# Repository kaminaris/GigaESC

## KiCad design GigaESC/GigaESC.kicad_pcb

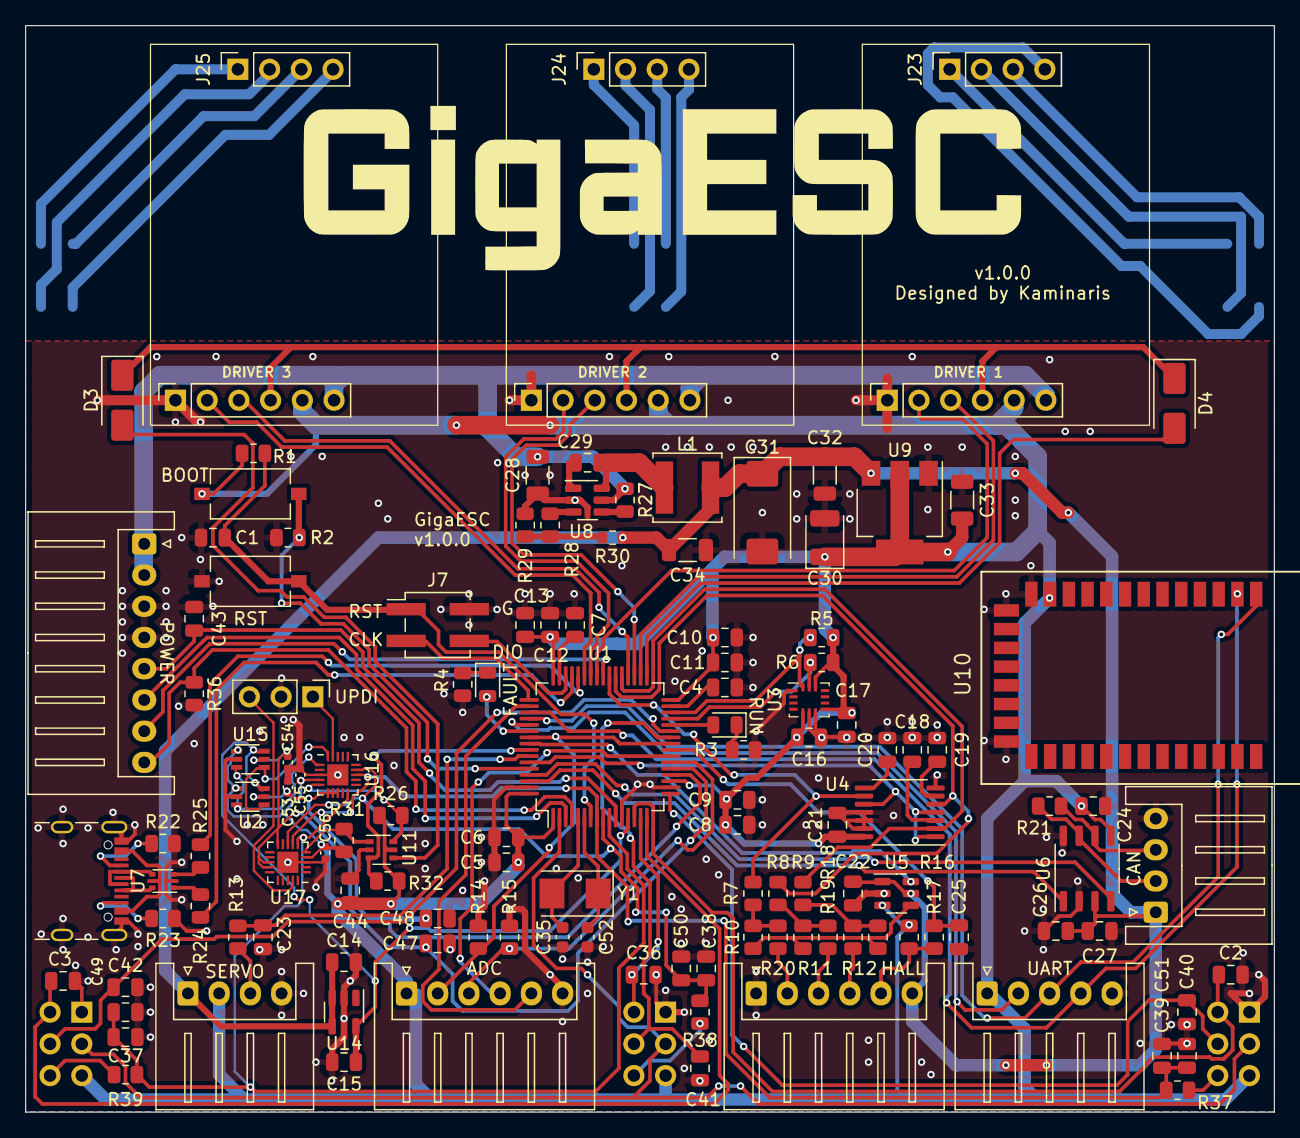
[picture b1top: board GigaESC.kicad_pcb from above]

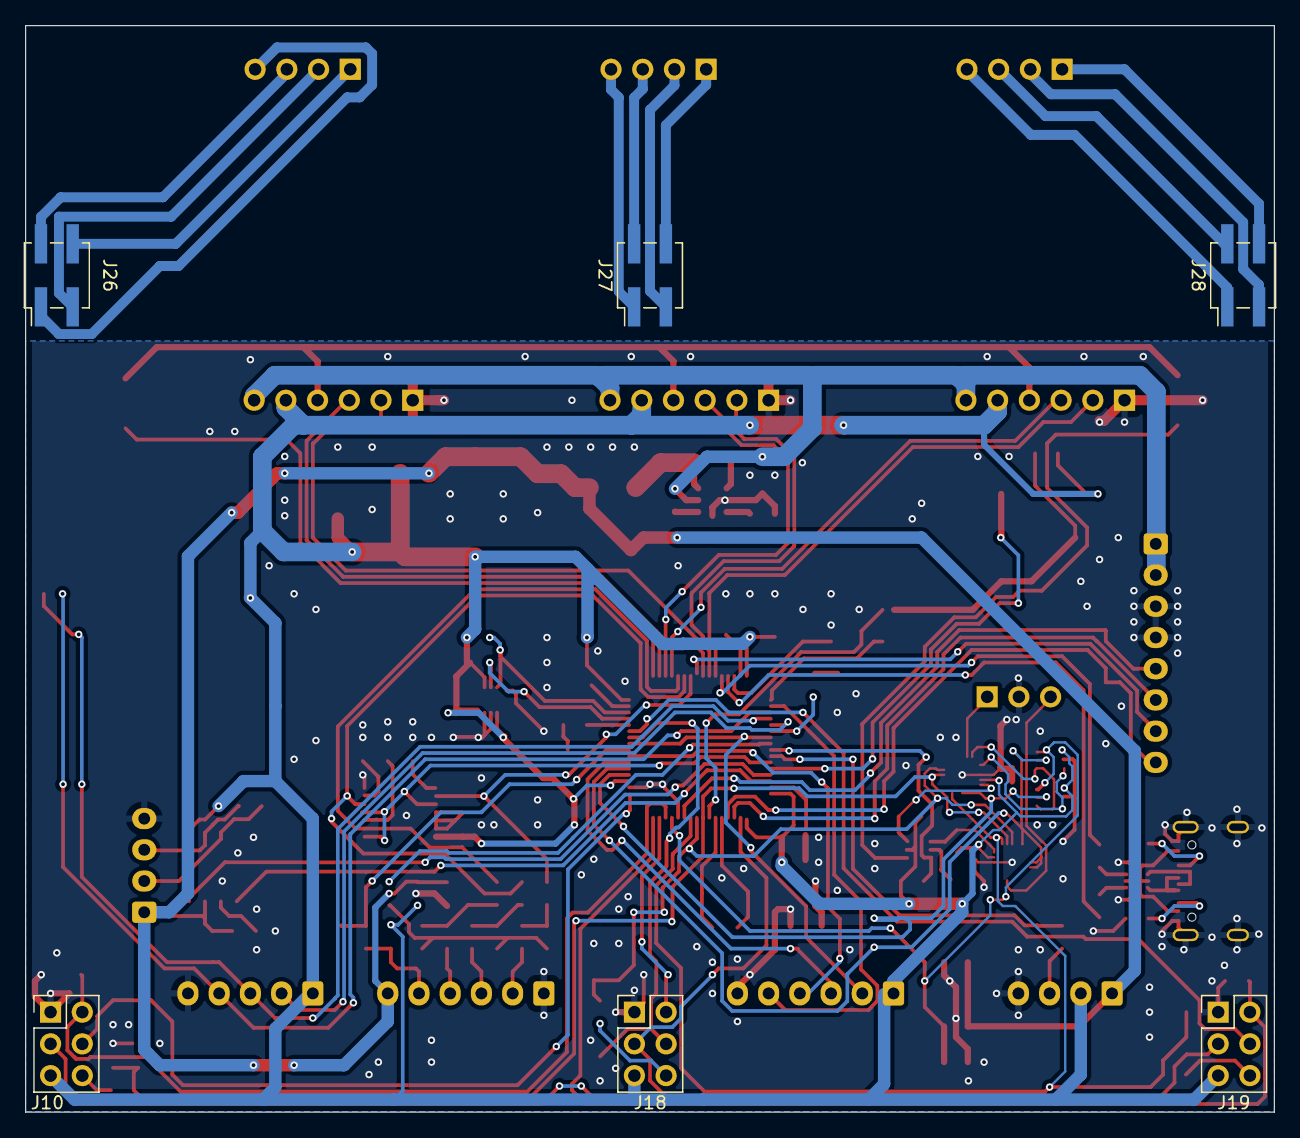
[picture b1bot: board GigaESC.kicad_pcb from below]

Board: 2 copper layers, 100.0 x 87.0 mm, 134 parts (6 on the bottom side), 110 nets.

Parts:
C1, C6, C9, C11, C13, C16, C17, C21, C22, C23, C24, C26, C44: 100n; C_0805_2012Metric
C2, C3, C36, C37, C38, C39, C40, C41, C42, C43: 1n; C_0805_2012Metric
C4, C7, C14, C15, C25, C47, C48: 1u; C_0805_2012Metric
C5, C8, C10, C12: 10n; C_0805_2012Metric
C18, C19, C20: 5n6; C_0805_2012Metric
C27: 2.2u; C_0805_2012Metric
C28: 47u 25V; C_1206_3216Metric
C29: 100n 100V; C_0805_2012Metric
C30: 100uF 6.3V Tant; CP_EIA-3528-15_AVX-H
C31: 100uF 25V Tant; CP_EIA-7343-31_Kemet-D
C32, C33, C34: 22u 25V; C_1206_3216Metric
C35, C52: 20p; C_0603_1608Metric
C49, C50, C51: 220p 50v; C_0805_2012Metric
C53, C54, C55, C56: 1u; C_0402_1005Metric
D1: L_RUN; LED_0805_2012Metric
D2: L_FAULT; LED_0805_2012Metric
D3, D4: SS14; D_SMA
J1: ServoConn; JST_XH_S4B-XH-A_1x04_P2.50mm_Horizontal
J2: AuxConn; JST_XH_S8B-XH-A_1x08_P2.50mm_Horizontal
J3, J14, J16: Input; PinSocket_1x06_P2.54mm_Vertical
J4: ADCConn; JST_XH_S6B-XH-A_1x06_P2.50mm_Horizontal
J5: HallConn; JST_XH_S6B-XH-A_1x06_P2.50mm_Horizontal
J6: UartSpi; JST_XH_S5B-XH-A_1x05_P2.50mm_Horizontal
J7: JTAG; PinHeader_2x02_P2.54mm_Vertical_SMD
J8: CANConn; JST_XH_S4B-XH-A_1x04_P2.50mm_Horizontal
J9: USBC Socket; USB_C_Receptacle_GCT_USB4105-xx-A_16P_TopMnt_Horizontal
J10, J18, J19: PhaseConn1; PinHeader_2x03_P2.54mm_Vertical
J12: UpdiConn; PinHeader_1x03_P2.54mm_Vertical
J23, J24, J25: Output; PinSocket_1x04_P2.54mm_Vertical
J26, J27, J28: OutputDown; PinHeader_2x02_P2.54mm_Vertical_SMD
L1: 5.6uH; L_Sunlord_SWPA5040S
R1, R3, R4, R14, R15, R16, R26, R31, R32, R36: 10k; R_0805_2012Metric
R2: 3.3k; R_0805_2012Metric
R5, R6: 4.7k; R_0805_2012Metric
R7, R8, R9, R10, R11, R12, R17, R37, R38, R39: 2.2k; R_0805_2012Metric
R13: 220; R_0805_2012Metric
R18, R19, R20: 100; R_0805_2012Metric
R21: 120; R_0805_2012Metric
R22, R23: 5.1k; R_0805_2012Metric
R24, R25: 22; R_0805_2012Metric
R27: 100k; R_0805_2012Metric
R28: 33k; R_0805_2012Metric
R29: 7.68k; R_0805_2012Metric
R30: 40.2k; R_0603_1608Metric
SW1: BOOT; SW_Tactile_SPST_NO_Straight_CK_PTS636Sx25SMTRLFS
SW3: RST; SW_Tactile_SPST_NO_Straight_CK_PTS636Sx25SMTRLFS
U1: STM32F405RGT6; LQFP-64_10x10mm_P0.5mm
U2: TPL0401A-10DCKR; Texas_R-PDSO-G6
U3: LSM6DS3TR-C; Bosch_LGA-14_3x2.5mm_P0.5mm
U4: SN74CBT3126PWR; TSSOP-14_4.4x5mm_P0.65mm
U5: RS2057XH; SOT-23-6
U6: TJA1051T-3; SOP-8_3.9x4.9mm_P1.27mm
U7: USBLC6-2P6; SOT-666
U8: ZTP7193Y; TSOT-23-6
U9: AMS1117-3.3; SOT-223-3_TabPin2
U10: HM-10; HM10
U11: SN74LVC1G332DCKR; SOT-363_SC-70-6
U14: LM4128AMF-3.3; SOT-23-5
U15: TPL0401B-10DCKR; Texas_R-PDSO-G6
U16, U17: ATTINY1616-MNR; VQFN-20-1EP_3x3mm_P0.4mm_EP1.7x1.7mm
Y1: X50328MSB2GI; Crystal_SMD_5032-2Pin_5.0x3.2mm

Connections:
+3.3V: C5.2, C6.2, C8.2, C9.2, C10.2, C11.2, C12.2, C13.2, C16.1, C17.1, C21.1, C24.1, C30.1, C33.1, C44.1, C55.1, C56.1, J1.2, J3.5, J4.1, J6.1, J10.5, J14.5, J16.5, J18.5, J19.5, R1.1, R5.1, R6.1, R16.1, R26.1, R31.1, R32.1, SW1.1, U1.1 (VBAT), U1.19 (VDD), U1.32 (VDD), U1.48 (VDD), U1.64 (VDD), U2.1 (VDD), U3.5 (VDDIO), U3.8 (VDD), U3.12 (CSB), U4.14 (VCC), U5.3 (NC), U6.5 (VIO), U9.2 (VO), U10.12 (VCC), U11.5 (VCC), U15.1 (VDD), U16.4 (VCC), U17.4 (VCC)
+3.3VADC: C15.1, U1.13 (VDDA), U2.6 (H), U14.5 (VREF), U15.6 (H)
+5V: C14.1, C22.1, C26.1, C27.1, C31.1, C32.1, C34.1, J1.1, J5.6, J8.1, L1.2, R30.2, U5.1 (NO), U5.5 (V+), U6.3 (VCC), U9.3 (VI), U14.3 (EN), U14.4 (VIN)
+15V: C28.1, J2.1, J2.2, J3.6, J14.6, J16.6, R27.1, U8.5 (IN)
/HardwareProtection/UPDI: J12.1, U16.19 (~RESET/PA0)
/HardwareProtection/UPDI2: J12.3, U17.19 (~RESET/PA0)
AUX_ENABLE: J2.6, U1.3 (PC14)
AUX_FAULT: J2.7, U1.40 (PC9)
BOOT: R2.1, SW1.2, U1.60 (BOOT0)
CANRx: U1.61 (PB8), U6.4 (RXD)
CANTx: U1.62 (PB9), U6.1 (TXD)
CLEAR_HW_FAULT: J2.8, R36.1, U1.4 (PC15)
CURR1: J10.6, R37.1
CURR1_FILTERED: C39.1, C51.1, R37.2, U1.8 (PC0), U16.13 (PB1), U17.7 (PA6)
CURR2: J18.6, R38.1
CURR2_FILTERED: C38.1, C50.1, R38.2, U1.9 (PC1), U16.14 (PB0), U17.8 (PA7)
CURR3: J19.6, R39.1
CURR3_FILTERED: C37.1, C49.1, R39.2, U1.10 (PC2), U16.10 (PB4), U17.6 (PA5)
CURR_TRIP_HIGH: C48.1, C53.1, U1.20 (PA4), U2.5 (W), U16.6 (PA5), U16.7 (PA6), U16.8 (PA7)
CURR_TRIP_LOW: C47.1, C54.1, U1.21 (PA5), U15.5 (W), U17.10 (PB4), U17.13 (PB1), U17.14 (PB0)
EXT2_MOSI: J6.2, U1.53 (PC12)
EXT2_RX_MISO: J6.3, U1.52 (PC11), U10.1 (UART_TX)
EXT2_TX_SCK: J6.4, U1.51 (PC10), U10.2 (UART_RX)
GND: C1.2, C2.2, C3.2, C4.2, C5.1, C6.1, C7.2, C8.1, C9.1, C10.1, C11.1, C12.1, C13.1, C14.2, C15.2, C16.2, C17.2, C18.2, C19.2, C20.2, C21.2, C22.2, C23.2, C24.2, C25.2, C26.2, C27.2, C28.2, C30.2, C31.2, C32.2, C33.2, C34.2, C35.1, C36.2, C37.2, C38.2, C39.2, C40.2, C41.2, C42.2, C43.2, C44.2, C47.2, C48.2, C49.2, C50.2, C51.2, C52.2, C53.2, C54.2, C55.2, C56.2, J1.4, J2.3, J2.4, J3.1, J4.6, J5.1, J6.5, J7.2, J8.4, J9.A1 (GND), J9.A12 (GND), J9.B1 (GND), J9.B12 (GND), J9.S1 (SHIELD), J10.1, J12.2, J14.1, J16.1, J18.1, J19.1, R2.2, R3.2, R4.2, R14.1, R15.1, R22.1, R23.1, R29.2, R36.2, SW3.2, U1.12 (VSSA), U1.18 (VSS), U1.63 (VSS), U2.2 (GND), U3.1 (SDO), U3.6 (GNDIO), U3.7 (GND), U4.7 (GND), U4.11 (4B), U4.12 (4A), U4.13 (4OEn), U5.2 (GND), U6.2 (GND), U6.8 (S), U7.2 (GND), U8.2 (GND), U9.1 (GND), U10.13 (GND), U10.14 (GND), U10.21 (GND), U11.2 (GND), U14.2 (GND), U15.2 (GND), U16.3 (GND), U16.21 (GND), U17.3 (GND), U17.21 (GND)
H1: J3.2, U1.41 (PA8)
H2: J14.2, U1.42 (PA9)
H3: J16.2, U1.43 (PA10)
HALL1: R9.1, U1.37 (PC6), U4.2 (1A)
HALL1_IN: R9.2, R12.2, R18.1
HALL2: R8.1, U1.38 (PC7), U4.5 (2A)
HALL2_IN: R8.2, R11.2, R19.1
HALL3: R7.1, U1.39 (PC8), U4.9 (3A)
HALL3_IN: R7.2, R10.2, R20.1
HALL_FILTER_ENABLE: U1.59 (PB7), U4.1 (1OEn), U4.4 (2OEn), U4.10 (3OEn)
IMU_SCL: R6.2, U1.29 (PB10), U3.13 (SCx)
IMU_SDA: R5.2, U1.30 (PB11), U3.14 (SDx)
IN_V: C43.1, J2.5, U1.11 (PC3)
L1: J3.3, U1.34 (PB13)
L2: J14.3, U1.35 (PB14)
L3: J16.3, U1.36 (PB15)
LED_FAULT: D2.2 (A), U1.54 (PD2)
LED_RUN: D1.2 (A), U1.28 (PB2)
MISO_ADC_EXT2: J4.3, R15.2, U1.22 (PA6)
MOSTEMP1: C40.1, J10.4, U1.17 (PA3)
MOSTEMP2: C41.1, J18.4, U1.26 (PB0)
MOSTEMP3: C42.1, J19.4, U1.27 (PB1)
NRST: C1.1, J7.1, R1.2, SW3.1, U1.7 (NRST)
unnamed: D1.1 (K), R3.1
unnamed: D2.1 (K), R4.1
unnamed: D3.2 (A), U11.4
unnamed: D4.2 (A), U1.33 (PB12)
unnamed: J1.3, R13.1
unnamed: J5.2, R20.2
unnamed: J5.3, R19.2
unnamed: J5.4, R18.2
unnamed: J8.2, R21.2, U6.7 (CANH)
unnamed: J8.3, R21.1, U6.6 (CANL)
unnamed: J9.A5 (CC1), R22.2
unnamed: J9.B5 (CC2), R23.2
unnamed: J9.A6 (D+), J9.B6 (D+), U7.6 (I/O1)
unnamed: J9.A7 (D-), J9.B7 (D-), U7.4 (I/O2)
unnamed: J23.1, J26.4
unnamed: J23.2, J26.3
unnamed: J23.3, J26.2
unnamed: J23.4, J26.1
unnamed: J24.1, J27.4
unnamed: J24.2, J27.3
unnamed: J24.3, J27.2
unnamed: J24.4, J27.1
unnamed: J25.1, J28.4
unnamed: J25.2, J28.3
unnamed: J25.3, J28.2
unnamed: J25.4, J28.1
unnamed: R24.1, U7.1 (I/O1)
unnamed: R25.1, U7.3 (I/O2)
unnamed: R28.2, R29.1, R30.1
unnamed: C35.2, U1.5 (PH0), Y1.2
unnamed: C52.1, U1.6 (PH1), Y1.1
unnamed: C4.1, U1.31 (VCAP_1)
unnamed: C7.1, U1.47 (VCAP_2)
unnamed: C18.1, U4.3 (1B)
unnamed: C19.1, U4.6 (2B)
unnamed: C20.1, U4.8 (3B)
unnamed: R10.1, R11.1, R12.1, U5.4 (COM)
unnamed: J9.A4 (VBUS), J9.A9 (VBUS), J9.B4 (VBUS), J9.B9 (VBUS), U7.5 (VBUS)
unnamed: C29.1, U8.1 (BOOT)
unnamed: R27.2, U8.4 (EN)
unnamed: R28.1, U8.3 (FB)
unnamed: C29.2, L1.1, U8.6 (SW)
unnamed: R26.2, U11.6, U16.5 (PA4)
unnamed: R31.2, U11.1, U17.5 (PA4)
POWER_STAGE_DISABLE: R32.2, U1.57 (PB5), U11.3
POWER_STAGE_LOCKOUT: D3.1 (K), D4.1 (K), J3.4, J14.4, J16.4
RX_SDA_NSS: J4.5, U1.50 (PA15)
SCK_ADC_EXT: J4.2, R14.2, U1.25 (PC5), U1.55 (PB3)
SCL: U2.3 (SCL), U15.3 (SCL), U16.1 (PA2)
SDA: U2.4 (SDA), U15.4 (SDA), U16.20 (PA1)
SENSOR_VOLTAGE_SELECT: U1.56 (PB4), U5.6 (IN)
SENS_FILTER_ENABLE: J10.3, J18.3, J19.3, U1.2 (PC13)
SERVO: C23.1, R13.2, U1.58 (PB6)
SWCLK: J7.3, U1.49 (PA14)
SWDIO: J7.4, U1.46 (PA13)
TEMPMOTOR: C25.1, R17.2, U1.24 (PC4)
TEMPMOTOR_IN: J5.5, R16.2, R17.1
TX_SCL_MOSI: J4.4, U1.23 (PA7)
USBD+: R24.2, U1.45 (PA12)
USBD-: R25.2, U1.44 (PA11)
VSENSE1: C2.1, J10.2, U1.14 (PA0)
VSENSE2: C36.1, J18.2, U1.15 (PA1)
VSENSE3: C3.1, J19.2, U1.16 (PA2)

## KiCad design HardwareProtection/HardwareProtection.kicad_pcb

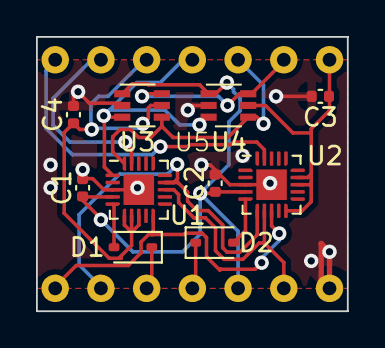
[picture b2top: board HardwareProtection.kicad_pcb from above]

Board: 2 copper layers, 17.3 x 15.2 mm, 11 parts (0 on the bottom side), 16 nets.

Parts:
C1, C2, C3, C4: 1u; C_0402_1005Metric
D1, D2: 1N5819WS; D_SOD-323
U1, U2: ATTINY1616-MNR; VQFN-20-1EP_3x3mm_P0.4mm_EP1.7x1.7mm
U3: TPL0401A-10DCKR; Texas_R-PDSO-G6
U4: TPL0401B-10DCKR; Texas_R-PDSO-G6
U5: HWProt

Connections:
+3.3V: C1.1, C2.1, U1.4 (VCC), U2.4 (VCC), U3.1 (VDD), U4.1 (VDD), U5.12 (+3.3V)
+3.3VADC: U3.6 (H), U4.6 (H), U5.6 (CURR_TRIP_LOW)
CURR1: U1.13 (PB1), U2.7 (PA6), U5.13 (+3.3VADC)
CURR2: U1.10 (PB4), U2.8 (PA7), U5.8 (CURR2)
CURR3: U1.14 (PB0), U2.6 (PA5), U5.9 (CURR3)
CURR_TRIP_HIGH: C4.1, U1.6 (PA5), U1.7 (PA6), U1.8 (PA7), U3.5 (W), U5.3 (SCL)
CURR_TRIP_LOW: C3.1, U2.10 (PB4), U2.13 (PB1), U2.14 (PB0), U4.5 (W), U5.7 (CURR1)
DISABLE: D2.1 (K), U5.11 (HW_OVERCURRENT)
GND: C1.2, C2.2, C3.2, C4.2, U1.3 (GND), U1.21 (GND), U2.3 (GND), U2.21 (GND), U3.2 (GND), U4.2 (GND), U5.14 (GND)
HW_OVERCURRENT: D1.1 (K), U5.10 (DISABLE)
unnamed: D1.2 (A), U1.5 (PA4)
unnamed: D2.2 (A), U2.5 (PA4)
SCL: U1.1 (PA2), U3.3 (SCL), U4.3 (SCL), U5.4 (SDA)
SDA: U1.20 (PA1), U3.4 (SDA), U4.4 (SDA), U5.5 (CURR_TRIP_HIGH)
UPDI: U1.19 (~RESET/PA0), U5.2 (UPDI2)
UPDI2: U2.19 (~RESET/PA0), U5.1 (UPDI)

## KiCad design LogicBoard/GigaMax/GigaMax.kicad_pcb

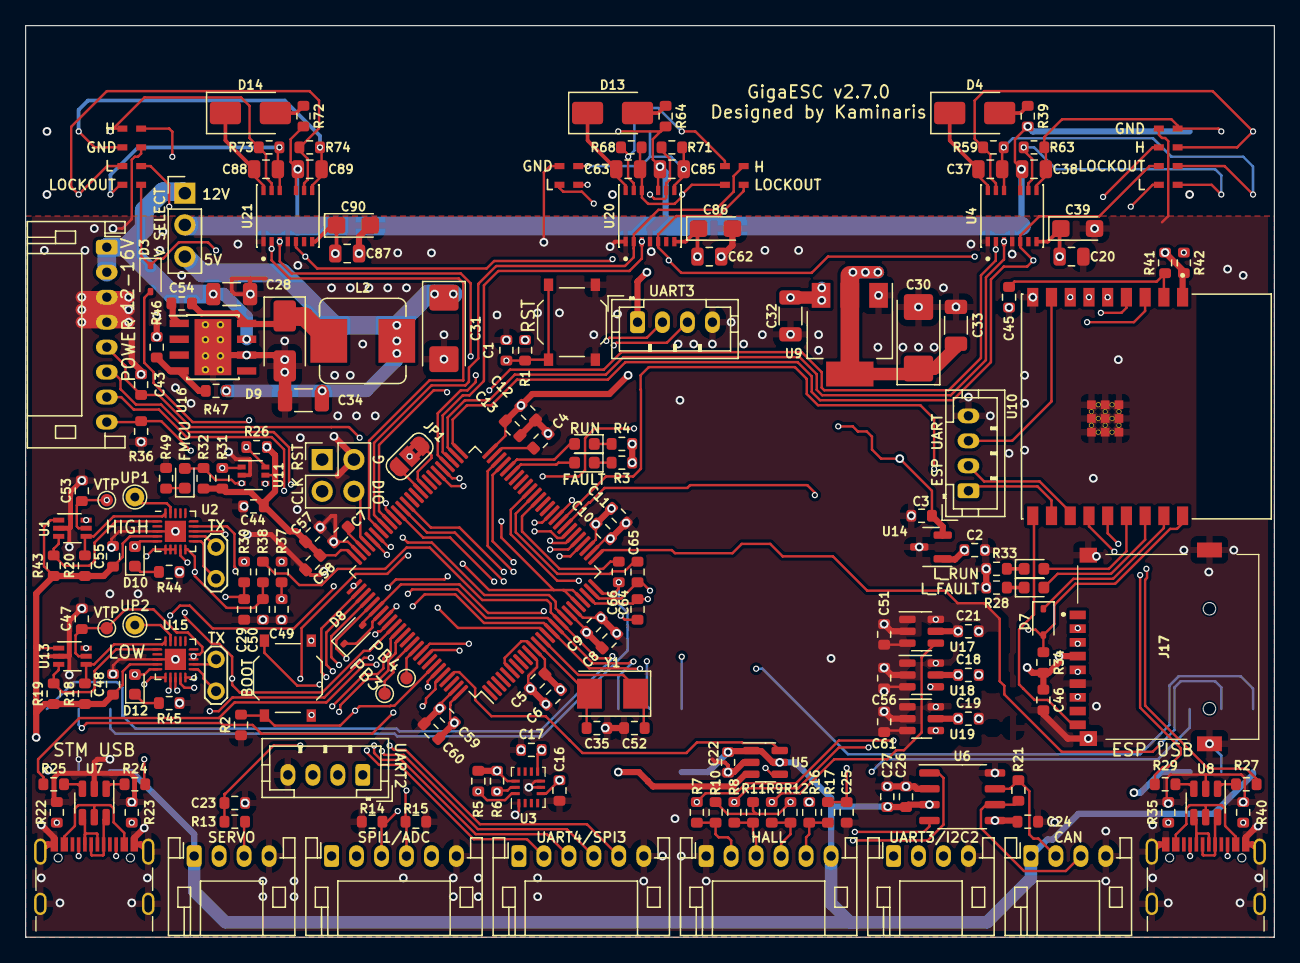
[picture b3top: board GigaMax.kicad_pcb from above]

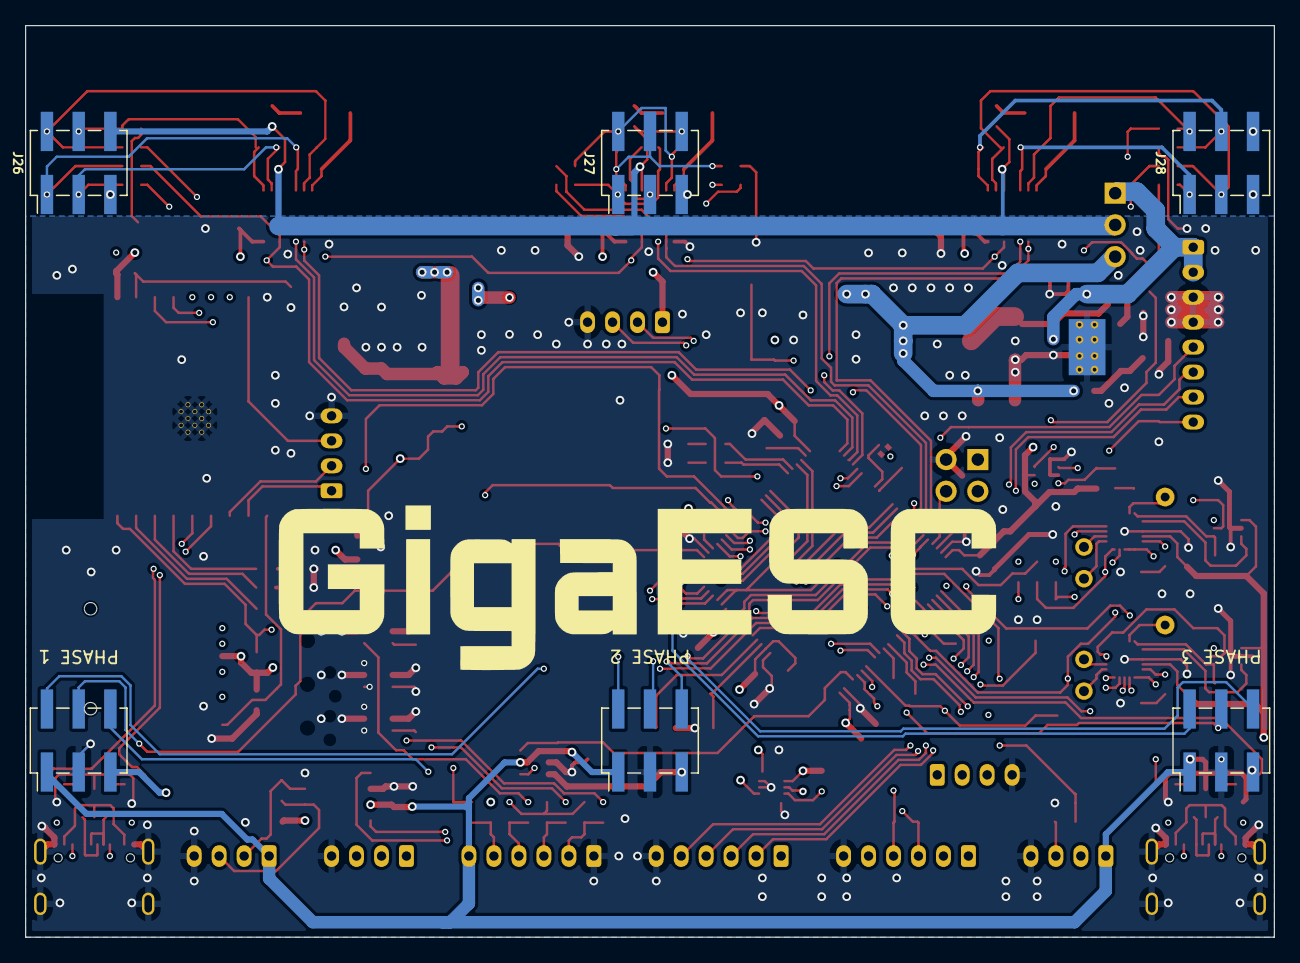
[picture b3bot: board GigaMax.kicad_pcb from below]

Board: 4 copper layers, 100.0 x 73.0 mm, 203 parts (6 on the bottom side), 159 nets.

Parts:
C1, C6, C9, C11, C13, C16, C17, C18, C19, C21, C22, C23, C24, C26, C44, C45, C46, C58, C60, C64, C65, C66: 100n; C_0603_1608Metric_L
C2, C3, C4, C7, C47, C48, C53, C55: 1u; C_0603_1608Metric_L
C5, C8, C10, C12, C54, C57, C59: 10n; C_0603_1608Metric_L
C20, C62, C87: 100n; C_0805_2012Metric
C25, C29, C43, C49, C50, C51, C56, C61: 1n; C_0603_1608Metric_L
C27: 2.2u; C_0603_1608Metric_L
C28, C32, C33, C34: 22u 25V; C_1206_3216Metric
C30, C31: 100uF 10V Tant; CP_EIA-6032-28_Kemet-C
C35, C52: 20p; R_0603_1608Metric
C37, C38, C63, C85, C88, C89: 4.7u 25v; C_0805_2012Metric
C39, C86, C90: 47u 6.3v Tant; CP_EIA-3216-18_Kemet-A
D1, D5: L_RUN; LED_0603_1608Metric
D2, D6, D10, D11, D12: L_FAULT; LED_0603_1608Metric
D3, D7, D8: 1N5819WS; D_SOD-323
D4, D13, D14: SS520F; D_SMA
D9: SS34; D_SMA
J1: ServoConn; JST_PH_S4B-PH-K_1x04_P2.00mm_Horizontal
J2: AuxConn; JST_PH_S8B-PH-K_1x08_P2.00mm_Horizontal
J3: DriverVoltageSelect; PinHeader_1x03_P2.54mm_Vertical
J4, J21: UARTDBG; TestPoint_2Pads_Pitch2.54mm_Drill0.8mm
J5: HallConn; JST_PH_S6B-PH-K_1x06_P2.00mm_Horizontal
J6: UARTConn; JST_PH_S4B-PH-K_1x04_P2.00mm_Horizontal
J7: JTAG; PinHeader_2x02_P2.54mm_Vertical
J8: CANConn; JST_PH_S4B-PH-K_1x04_P2.00mm_Horizontal
J9, J13: USBC Socket; USB_C_Receptacle_GCT_USB4105-xx-A_16P_TopMnt_Horizontal
J10, J18, J19, J26, J27, J28: PhaseConn1; PinHeader_2x03_P2.54mm_Vertical_SMD
J11, J20: SPI1Conn; JST_PH_S6B-PH-K_1x06_P2.00mm_Horizontal
J12: UART2Conn; JST_PH_B4B-PH-K_1x04_P2.00mm_Vertical
J15: ESPUartConn; JST_PH_B4B-PH-K_1x04_P2.00mm_Vertical
J17: MicroSD; TF01A
J22: UART3Conn; JST_PH_B4B-PH-K_1x04_P2.00mm_Vertical
JP1: ServoSelector; SolderJumper-3_P1.3mm_Bridged2Bar12_RoundedPad1.0x1.5mm_Num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
JP2, JP3, JP4, JP5, JP6, JP7, JP8, JP9, JP10, JP11, JP12, JP13: DirectJump; SolderJumper0.5mm_Open
L2: 15uH; L_Bourns_SRP7028A_7.3x6.6mm
R1, R3, R4, R7, R8, R9, R10, R11, R12, R14, R15, R16, R17, R26, R28, R31, R32, R33, R34, R36, R41, R42, R44, R45, R47, R49: 10k; R_0603_1608Metric
R2, R46: 3.3k; R_0603_1608Metric
R5, R6, R18, R19, R20, R43, R59, R63, R68, R71, R73, R74: 4.7k; R_0603_1608Metric
R13: 220; R_0603_1608Metric
R21: 120; R_0603_1608Metric
R22, R23, R35, R40: 5.1k; R_0603_1608Metric
R24, R25, R27, R29: 22; R_0603_1608Metric
R30, R37, R38: 1k; R_0603_1608Metric
R39, R64, R72: 2.2; R_0603_1608Metric
SW1: BOOT; SW_Push_1P1T_XKB_TS-1187A
SW3: RST; SW_Push_1P1T_XKB_TS-1187A
TP1, TP2: TestPoint; TestPoint_Pad_D1.0mm
TP3, TP4: VTP; TestPoint_Pad_D1.0mm
TP5, TP6: UPDI; TestPoint_THTPad_D1.5mm_Drill0.7mm
U1, U13: TPL0401B-10DCKR; Texas_R-PDSO-G6
U2, U15: ATTINY1616-MNR; VQFN-20-1EP_3x3mm_P0.4mm_EP1.7x1.7mm
U3: LSM6DS3TR-C; Bosch_LGA-14_3x2.5mm_P0.5mm
U4, U20, U21: 2EDF7275KXUMA1; IC_2EDF7275KXUMA2
U5, U17, U18, U19: RS2057XH; SOT-23-6
U6: TJA1050T/CM,118; SOP-8_3.9x4.9mm_P1.27mm
U7, U8: USBLC6-2SC6; SOT-23-6
U9: AMS1117-3.3; SOT-223-3_TabPin2
U10: ESP32-C3-WROOM-02-N4; MODULE_ESP32-C3-WROOM-02-H4
U11: SN74LVC1G332DCKR; SOT-363_SC-70-6
U12: STM32F407VGT6; LQFP-100_14x14mm_P0.5mm
U14: REF3033AIDBZR; SOT-23
U16: TPS5430DDAR; TI_SO-PowerPAD-8_ThermalVias
Y1: X50328MSB2GI; Crystal_SMD_5032-2Pin_5.0x3.2mm

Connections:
+3.3REF: C3.1, U1.6 (H), U12.21 (VREF+), U12.22 (VDDA), U13.6 (H), U14.2 (Vout)
+3.3V: C5.1, C6.1, C8.1, C9.1, C10.1, C11.1, C12.1, C13.1, C16.1, C17.1, C18.1, C19.1, C20.2, C21.1, C24.1, C30.1, C33.1, C39.1, C44.1, C46.1, C48.1, C55.1, C57.1, C58.1, C59.1, C60.1, C62.2, C86.1, C87.2, C90.1, J1.2, J6.1, J10.5, J11.1, J12.1, J17.4 (VDD), J18.5, J19.5, J20.1, J22.1, J26.5, J27.5, J28.5, R1.1, R5.1, R6.1, R16.2, R18.1, R19.1, R20.1, R26.1, R31.1, R32.1, R34.1, R41.2, R42.1, R43.1, SW1.1, U1.1 (VDD), U2.4 (VCC), U3.5 (VDDIO), U3.8 (VDD), U3.12 (CSB), U4.7 (VDDI), U5.3 (NC), U6.5 (VIO), U9.2 (VO), U10.1 (3V3), U11.5 (VCC), U12.6 (VBAT), U12.11 (VDD), U12.19 (VDD), U12.28 (VDD), U12.50 (VDD), U12.75 (VDD), U12.100 (VDD), U13.1 (VDD), U15.4 (VCC), U17.5 (V+), U18.5 (V+), U19.5 (V+), U20.7 (VDDI), U21.7 (VDDI)
+5V: C2.1, C22.1, C26.1, C27.1, C31.1, C32.1, C34.1, J1.1, J3.3, J5.6, J8.1, J10.1, J18.1, J19.1, L2.2, R47.2, U5.1 (NO), U5.5 (V+), U6.3 (VCC), U9.3 (VI), U14.1 (Vin)
+15V: C28.1, J2.1, J2.2, J3.1, U16.7 (VIN)
/DriverSocketPhase1/GND_OUT: C38.2, J26.4, JP9.1 (A), R63.1, U4.8 (GNDB)
/DriverSocketPhase1/H_OUT: J26.2, JP8.1 (A), R59.2, U4.12 (OUTA)
/DriverSocketPhase1/LOCKOUT: C37.2, J26.1, JP2.1 (A), R59.1, U4.11 (GNDA)
/DriverSocketPhase1/L_OUT: J26.3, JP5.1 (A), R63.2, U4.9 (OUTB)
/DriverSocketPhase2/GND_OUT: C85.2, J27.4, JP11.1 (A), R71.1, U20.8 (GNDB)
/DriverSocketPhase2/H_OUT: J27.2, JP10.1 (A), R68.2, U20.12 (OUTA)
/DriverSocketPhase2/LOCKOUT: C63.2, J27.1, JP3.1 (A), R68.1, U20.11 (GNDA)
/DriverSocketPhase2/L_OUT: J27.3, JP6.1 (A), R71.2, U20.9 (OUTB)
/DriverSocketPhase3/GND_OUT: C89.2, J28.4, JP13.1 (A), R74.1, U21.8 (GNDB)
/DriverSocketPhase3/H_OUT: J28.2, JP12.1 (A), R73.2, U21.12 (OUTA)
/DriverSocketPhase3/LOCKOUT: C88.2, J28.1, JP4.1 (A), R73.1, U21.11 (GNDA)
/DriverSocketPhase3/L_OUT: J28.3, JP7.1 (A), R74.2, U21.9 (OUTB)
/HardwareProtection/ComparatorHigh/ATTINY_SCL: R43.2, U1.3 (SCL), U2.1 (PA2)
/HardwareProtection/ComparatorHigh/ATTINY_SDA: R20.2, U1.4 (SDA), U2.20 (PA1)
/HardwareProtection/ComparatorHigh/AT_RX: J21.2, U2.11 (PB3)
/HardwareProtection/ComparatorHigh/AT_TX: J21.1, U2.12 (PB2)
/HardwareProtection/ComparatorHigh/CMP1-: C53.1, TP3.1, U1.5 (W), U2.6 (PA5), U2.7 (PA6), U2.8 (PA7)
/HardwareProtection/ComparatorHigh/LATCH_OUT: D10.2 (A), R26.2, U2.5 (PA4), U11.6
/HardwareProtection/ComparatorLow/ATTINY_SCL: R19.2, U13.3 (SCL), U15.1 (PA2)
/HardwareProtection/ComparatorLow/ATTINY_SDA: R18.2, U13.4 (SDA), U15.20 (PA1)
/HardwareProtection/ComparatorLow/AT_RX: J4.2, U15.11 (PB3)
/HardwareProtection/ComparatorLow/AT_TX: J4.1, U15.12 (PB2)
/HardwareProtection/ComparatorLow/CMP1+: C47.1, TP4.1, U13.5 (W), U15.10 (PB4), U15.13 (PB1), U15.14 (PB0)
/HardwareProtection/ComparatorLow/LATCH_OUT: D12.2 (A), R31.2, U11.1, U15.5 (PA4)
ADC_EXT: J11.3, R14.2, U12.30 (PA5)
ADC_EXT2: J11.4, R15.1, U12.31 (PA6)
AUX_ENABLE: J2.6, U12.83 (PD2)
AUX_FAULT: J2.7, U12.84 (PD3)
BOOT: R2.1, SW1.2, U12.94 (BOOT0)
CAN2_RX: D7.2 (A), D8.2 (A), R34.2, U10.18 (IO0), U12.81 (PD0)
CAN2_TX: D8.1 (K), U12.82 (PD1)
CAN_RX: U6.4 (RXD), U12.91 (PB5)
CAN_TX: U6.1 (TXD), U12.92 (PB6)
CLEAR_HW_FAULT: J2.8, R36.1, U2.9 (PB5), U12.85 (PD4), U15.9 (PB5)
CURR1: J10.6, R30.2, U12.15 (PC0)
CURR1_FILTERED: C29.1, R30.1, U2.13 (PB1), U15.7 (PA6)
CURR2: J18.6, R37.2, U12.16 (PC1)
CURR2_FILTERED: C49.1, R37.1, U2.14 (PB0), U15.8 (PA7)
CURR3: J19.6, R38.2, U12.17 (PC2)
CURR3_FILTERED: C50.2, R38.1, U2.10 (PB4), U15.6 (PA5)
DRIVER_POWER: C38.1, C85.1, C89.1, J3.2, J26.6, J27.6, J28.6, R39.1, R64.1, R72.1, U4.10 (VDDB), U20.10 (VDDB), U21.10 (VDDB)
ESP_FAULT_LED: D6.2 (A), U10.16 (IO2)
ESP_IO9: J15.3, U10.8 (IO9)
ESP_MISO: J17.7 (DAT0), U10.5 (IO6)
ESP_MOSI: J17.3 (CMD), U10.3 (IO4)
ESP_RUN_LED: D5.2 (A), U10.15 (IO3)
ESP_RX: J15.1, U10.11 (RXD)
ESP_SCK: J17.5 (CLK), U10.4 (IO5)
ESP_SD_CS: J17.2 (DAT3/CD), U10.6 (IO7)
ESP_SD_DETECT: J17.9 (DET), U10.10 (IO10)
ESP_TX: J15.2, U10.12 (TXD)
ESP_USB_D+: R27.2, U10.14 (IO19)
ESP_USB_D-: R29.2, U10.13 (IO18)
FLOAT_VDD1: C37.1, D4.1 (K), U4.13 (VDDA)
FLOAT_VDD2: C63.1, D13.1 (K), U20.13 (VDDA)
FLOAT_VDD3: C88.1, D14.1 (K), U21.13 (VDDA)
GND: C1.2, C2.2, C3.2, C4.2, C5.2, C6.2, C7.2, C8.2, C9.2, C10.2, C11.2, C12.2, C13.2, C16.2, C17.2, C18.2, C19.2, C20.1, C21.2, C22.2, C23.2, C24.2, C25.2, C26.2, C27.2, C28.2, C29.2, C30.2, C31.2, C32.2, C33.2, C34.2, C35.1, C39.2, C43.2, C44.2, C45.2, C46.2, C47.2, C48.2, C49.2, C50.1, C51.1, C52.2, C53.2, C55.2, C56.1, C57.2, C58.2, C59.2, C60.2, C61.1, C62.1, C86.2, C87.1, C90.2, D9.2 (A), J1.4, J2.3, J2.4, J5.1, J6.4, J7.2, J8.4, J9.A1 (GND), J9.A12 (GND), J9.B1 (GND), J9.B12 (GND), J9.S1 (SHIELD), J10.3, J11.6, J12.4, J13.A1 (GND), J13.A12 (GND), J13.B1 (GND), J13.B12 (GND), J13.S1 (SHIELD), J15.4, J17.6 (VSS), J17.10 (SHIELD), J18.3, J19.3, J20.6, J22.4, JP9.2 (B), JP11.2 (B), JP13.2 (B), R2.2, R3.2, R4.2, R14.1, R15.2, R22.1, R23.1, R28.2, R33.2, R35.1, R36.2, R40.1, R44.2, R45.2, R46.2, R49.2, SW3.2, U1.2 (GND), U2.3 (GND), U2.21 (GND), U3.1 (SDO), U3.6 (GNDIO), U3.7 (GND), U4.1 (GNDI), U4.4 (SLDON), U5.2 (GND), U6.2 (GND), U6.8 (S), U7.2 (GND), U8.2 (GND), U9.1 (GND), U10.9 (GND), U10.19 (GND), U10.20 (GND), U10.21 (GND), U10.22 (GND), U10.23 (GND), U10.24 (GND), U10.25 (GND), U10.26 (GND), U10.27 (GND), U10.28 (GND), U10.29 (GND), U10.30 (GND), U10.31 (GND), U10.32 (GND), U10.33 (GND), U10.34 (GND), U10.35 (GND), U10.36 (GND), U10.37 (GND), U10.38 (GND), U10.39 (GND), U11.2 (GND), U12.10 (VSS), U12.20 (VSSA), U12.27 (VSS), U12.74 (VSS), U12.99 (VSS), U13.2 (GND), U14.3 (GND), U15.3 (GND), U15.21 (GND), U16.6 (GND), U16.9 (GNDPAD), U17.2 (GND), U18.2 (GND), U19.2 (GND), U20.1 (GNDI), U20.4 (SLDON), U21.1 (GNDI), U21.4 (SLDON)
H1: JP8.2 (B), U4.2 (INA), U12.67 (PA8)
H2: JP10.2 (B), U12.68 (PA9), U20.2 (INA)
H3: JP12.2 (B), U12.69 (PA10), U21.2 (INA)
HALL1: R9.1, U12.63 (PC6), U17.4 (COM)
HALL1_IN: J5.4, R9.2, R12.1
HALL2: R8.1, U12.64 (PC7), U18.4 (COM)
HALL2_IN: J5.3, R8.2, R11.1
HALL3: R7.1, U12.65 (PC8), U19.4 (COM)
HALL3_IN: J5.2, R7.2, R10.1
HALL_FILTER_ENABLE: U12.34 (PC5), U17.6 (IN), U18.6 (IN), U19.6 (IN)
I2C2_SCL/USART3_TX: J6.2, U12.47 (PB10)
I2C2_SDA/USART3_RX: J6.3, U12.48 (PB11)
IMU_SCL: R6.2, U3.13 (SCx), U12.95 (PB8)
IMU_SDA: R5.2, U3.14 (SDx), U12.96 (PB9)
IN_V: C43.1, J2.5, U12.18 (PC3)
L1: JP5.2 (B), U4.3 (INB), U12.52 (PB13)
L2: JP6.2 (B), U12.53 (PB14), U20.3 (INB)
L3: JP7.2 (B), U12.54 (PB15), U21.3 (INB)
LED_FAULT: D2.2 (A), U12.46 (PE15)
LED_RUN: D1.2 (A), U12.45 (PE14)
MOSTEMP1: J10.4, U12.26 (PA3)
MOSTEMP2: J18.4, U12.35 (PB0)
MOSTEMP3: J19.4, U12.36 (PB1)
NRST: C1.1, J7.1, R1.2, SW3.1, U12.14 (NRST)
unnamed: D1.1 (K), R3.1
unnamed: D2.1 (K), R4.1
unnamed: D3.2 (A), U11.4
unnamed: D4.2 (A), R39.2
unnamed: D5.1 (K), R33.1
unnamed: D6.1 (K), R28.1
unnamed: D7.1 (K), U10.17 (IO1)
unnamed: C54.1, D9.1 (K), L2.1, U16.8 (PH)
unnamed: D10.1 (K), R44.1
unnamed: D11.1 (K), R49.1
unnamed: D12.1 (K), R45.1
unnamed: D13.2 (A), R64.2
unnamed: D14.2 (A), R72.2
unnamed: J1.3, R13.1
unnamed: J8.2, R21.2, U6.7 (CANH)
unnamed: J8.3, R21.1, U6.6 (CANL)
unnamed: J9.A5 (CC1), R22.2
unnamed: J9.B5 (CC2), R23.2
unnamed: J9.A6 (D+), J9.B6 (D+), U7.6 (I/O1)
unnamed: J9.A7 (D-), J9.B7 (D-), U7.4 (I/O2)
unnamed: J13.A5 (CC1), R35.2
unnamed: J13.B5 (CC2), R40.2
unnamed: J13.A6 (D+), J13.B6 (D+), U8.6 (I/O1)
unnamed: J13.A7 (D-), J13.B7 (D-), U8.4 (I/O2)
unnamed: JP1.1 (A), U12.59 (PD12)
unnamed: JP1.3 (B), U12.60 (PD13)
unnamed: R24.1, U7.1 (I/O1)
unnamed: R25.1, U7.3 (I/O2)
unnamed: R27.1, U8.1 (I/O1)
unnamed: R29.1, U8.3 (I/O2)
unnamed: TP5.1, U2.19 (~RESET/PA0)
unnamed: R10.2, R11.2, R12.2, U5.4 (COM)
unnamed: J9.A4 (VBUS), J9.A9 (VBUS), J9.B4 (VBUS), J9.B9 (VBUS), U7.5 (VBUS)
unnamed: J13.A4 (VBUS), J13.A9 (VBUS), J13.B4 (VBUS), J13.B9 (VBUS), U8.5 (VBUS)
unnamed: C45.1, R41.1, U10.2 (EN)
unnamed: R42.2, U10.7 (IO8)
unnamed: TP1.1, U12.89 (PB3)
unnamed: TP2.1, U12.90 (PB4)
unnamed: C35.2, U12.12 (PH0), Y1.2
unnamed: C52.1, U12.13 (PH1), Y1.1
unnamed: C4.1, U12.49 (VCAP_1)
unnamed: C7.1, U12.73 (VCAP_2)
unnamed: TP6.1, U15.19 (~RESET/PA0)
unnamed: C54.2, U16.1 (BOOT)
unnamed: R46.1, R47.1, U16.4 (VSENSE)
unnamed: C51.2, U17.3 (NC)
unnamed: C56.2, U18.3 (NC)
unnamed: C61.2, U19.3 (NC)
PHASE_FILTER_ENABLE1: C64.2, U12.41 (PE10)
PHASE_FILTER_ENABLE2: C65.2, U12.40 (PE9)
PHASE_FILTER_ENABLE3: C66.2, U12.39 (PE8)
POWER_STAGE_DISABLE: D11.2 (A), R32.2, U11.3, U12.66 (PC9)
POWER_STAGE_LOCKOUT: D3.1 (K), JP2.2 (B), JP3.2 (B), JP4.2 (B), U4.5 (DISABLE), U12.51 (PB12), U20.5 (DISABLE), U21.5 (DISABLE)
SENSOR_VOLTAGE_SELECT: U5.6 (IN), U12.97 (PE0)
SERVO: C23.1, JP1.2 (C), R13.2
SPI1_MOSI: J11.5, U12.32 (PA7)
SPI1_NSS: J11.2, U12.29 (PA4)
SPI3_MISO: J20.4, U12.79 (PC11)
SPI3_MOSI: J20.5, U12.80 (PC12)
SPI3_NSS: J20.2, U12.77 (PA15)
SPI3_SCK: J20.3, U12.78 (PC10)
SWCLK: J7.3, U12.76 (PA14)
SWDIO: J7.4, U12.72 (PA13)
TEMPMOTOR: C25.1, R17.2, U12.33 (PC4)
TEMPMOTOR_IN: J5.5, R16.1, R17.1
UART3_RX: J22.3, U12.56 (PD9)
UART3_TX: J22.2, U12.55 (PD8)
USART2_RX: J12.3, U12.87 (PD6)
USART2_TX: J12.2, U12.86 (PD5)
USBD+: R24.2, U12.71 (PA12)
USBD-: R25.2, U12.70 (PA11)
VSENSE1: C64.1, J10.2, U12.23 (PA0)
VSENSE2: C65.1, J18.2, U12.24 (PA1)
VSENSE3: C66.1, J19.2, U12.25 (PA2)

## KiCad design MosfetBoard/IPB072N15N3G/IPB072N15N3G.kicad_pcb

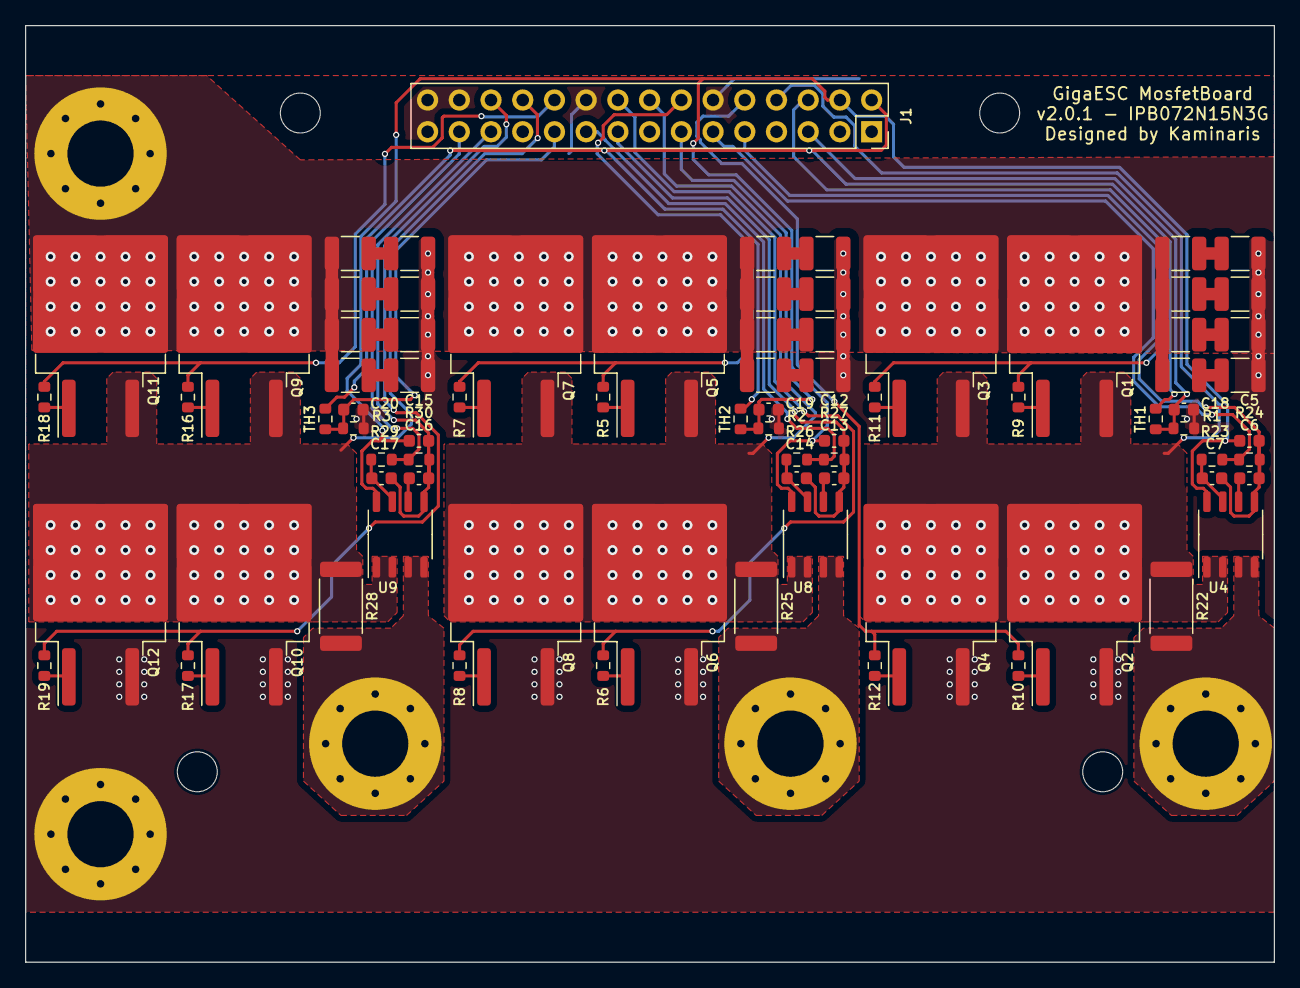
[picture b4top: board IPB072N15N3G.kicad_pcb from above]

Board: 2 copper layers, 100.0 x 75.0 mm, 88 parts (0 on the bottom side), 55 nets.

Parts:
C1, C2, C3, C4, C8, C9, C10, C11, C25, C26, C27, C28, C30, C31, C32, C33, C48, C49, C50, C51, C52, C53, C54, C55: 10u 100V; C_1210_3225Metric
C5, C12, C15: 100n; C_0603_1608Metric
C6, C13, C16: 10n; C_0603_1608Metric
C7, C14, C17: 1n; C_0603_1608Metric
C18, C19, C20: 1u; C_0603_1608Metric
H1, H2, H3, H4, H5: MountingHole_Pad; MountingHole_5.3mm_M5_Pad_Via
H6, H7, H8, H9: MountingHole; MountingHole_3.2mm_M3_ISO14580
J1: LogicConnector; PinSocket_2x15_P2.54mm_Vertical
Q1, Q2, Q3, Q4, Q5, Q6, Q7, Q8, Q9, Q10, Q11, Q12: IPB072N15N3G; TO-263-2
R1, R2, R3: 10k; R_0603_1608Metric
R5, R6, R7, R8, R9, R10, R11, R12, R16, R17, R18, R19: 2.2; R_0603_1608Metric
R22, R25, R28: 0.3m; R_2512_6332Metric
R23, R26, R29: 4.7k; R_0603_1608Metric
R24, R27, R30: 9.1k; R_0603_1608Metric
TH1, TH2, TH3: NCP18XH103F03RB; R_0603_1608Metric
U4, U8, U9: MT9223CT-50BR5; SOP-8_3.9x4.9mm_P1.27mm

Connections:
+BATT: C1.1, C8.1, C10.1, C25.1, C26.1, C28.1, C31.1, C33.1, C48.1, C50.1, C52.1, C54.1, H5.1, Q1.2 (D), Q3.2 (D), Q5.2 (D), Q7.2 (D), Q9.2 (D), Q11.2 (D)
-BATT: C2.2, C3.2, C4.2, C9.2, C11.2, C18.2, C19.2, C20.2, C27.2, C30.2, C32.2, C49.2, C51.2, C53.2, C55.2, H4.1, J1.12, J1.20, J1.28, J1.29, J1.30, Q2.3 (S), Q4.3 (S), Q6.3 (S), Q8.3 (S), Q10.3 (S), Q12.3 (S), R1.2, R2.2, R3.2
/3.3V: J1.2, TH1.1, TH2.1, TH3.1
/5V: C5.2, C12.2, C15.2, J1.4, U4.8 (VCC), U8.8 (VCC), U9.8 (VCC)
/PH1: J1.6, R9.1, R11.1
/PH2: J1.14, R5.1, R7.1
/PH3: J1.22, R16.1, R18.1
/PHASE1: J1.8, Q1.3 (S), Q2.2 (D), Q3.3 (S), Q4.2 (D), R22.2, U4.1 (IP+), U4.2 (IP+)
/PHASE2: J1.16, Q5.3 (S), Q6.2 (D), Q7.3 (S), Q8.2 (D), R25.2, U8.1 (IP+), U8.2 (IP+)
/PHASE3: J1.24, Q9.3 (S), Q10.2 (D), Q11.3 (S), Q12.2 (D), R28.2, U9.1 (IP+), U9.2 (IP+)
/PL1: J1.10, R10.1, R12.1
/PL2: J1.18, R6.1, R8.1
/PL3: J1.26, R17.1, R19.1
/PhaseMosfets1/MOS_TEMP: C18.1, J1.5, R1.1, TH1.2
/PhaseMosfets1/PHASE_OUT: H1.1, R22.1, U4.3 (IP-), U4.4 (IP-)
/PhaseMosfets1/SH+: J1.11, R23.1, R24.2
/PhaseMosfets1/SH-: C5.1, C6.2, C7.2, J1.9, R24.1, U4.5 (GND)
/PhaseMosfets2/MOS_TEMP: C19.1, J1.13, R2.1, TH2.2
/PhaseMosfets2/PHASE_OUT: H2.1, R25.1, U8.3 (IP-), U8.4 (IP-)
/PhaseMosfets2/SH+: J1.19, R26.1, R27.2
/PhaseMosfets2/SH-: C12.1, C13.2, C14.2, J1.17, R27.1, U8.5 (GND)
/PhaseMosfets3/MOS_TEMP: C20.1, J1.21, R3.1, TH3.2
/PhaseMosfets3/PHASE_OUT: H3.1, R28.1, U9.3 (IP-), U9.4 (IP-)
/PhaseMosfets3/SH+: J1.27, R29.1, R30.2
/PhaseMosfets3/SH-: C15.1, C16.2, C17.2, J1.25, R30.1, U9.5 (GND)
unnamed: C1.2, C2.1
unnamed: C4.1, C48.2
unnamed: C8.2, C9.1
unnamed: C10.2, C11.1
unnamed: C3.1, C25.2
unnamed: C26.2, C27.1
unnamed: C28.2, C30.1
unnamed: C31.2, C32.1
unnamed: C33.2, C49.1
unnamed: C50.2, C51.1
unnamed: C52.2, C53.1
unnamed: C54.2, C55.1
unnamed: Q1.1 (G), R9.2
unnamed: Q2.1 (G), R10.2
unnamed: Q3.1 (G), R11.2
unnamed: Q4.1 (G), R12.2
unnamed: Q5.1 (G), R5.2
unnamed: Q6.1 (G), R6.2
unnamed: Q7.1 (G), R7.2
unnamed: Q8.1 (G), R8.2
unnamed: Q9.1 (G), R16.2
unnamed: Q10.1 (G), R17.2
unnamed: Q11.1 (G), R18.2
unnamed: Q12.1 (G), R19.2
unnamed: C6.1, U4.6 (FILTER)
unnamed: C7.1, R23.2, U4.7 (VIOUT)
unnamed: C13.1, U8.6 (FILTER)
unnamed: C14.1, R26.2, U8.7 (VIOUT)
unnamed: C16.1, U9.6 (FILTER)
unnamed: C17.1, R29.2, U9.7 (VIOUT)
